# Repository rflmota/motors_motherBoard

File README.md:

# motors_motherBoard
## Carrier board for dual *[STM's L6470](https://www.st.com/en/motor-drivers/l6470.html)* stepper motor driver controller with *[Teensy 3.6](https://www.pjrc.com/teensy/)* interface. This project was applied for control a two-wheel differential drive mobile robot.

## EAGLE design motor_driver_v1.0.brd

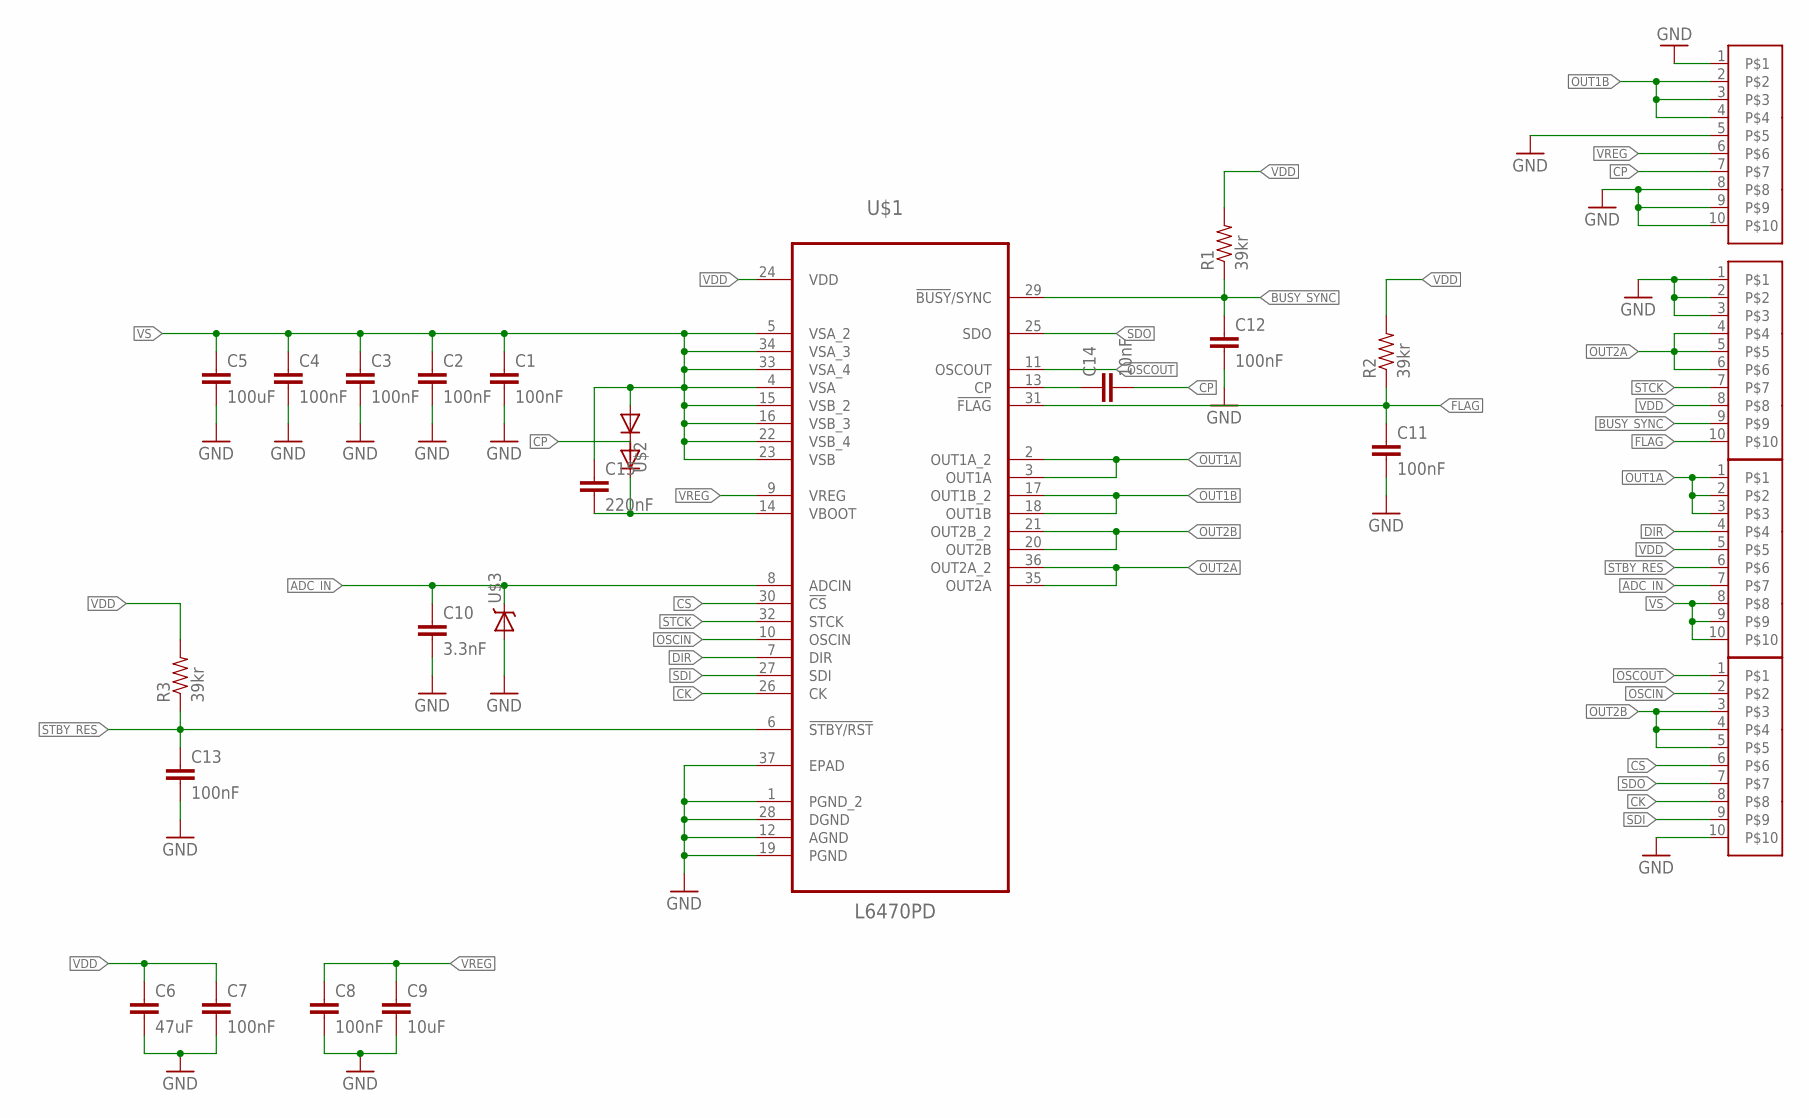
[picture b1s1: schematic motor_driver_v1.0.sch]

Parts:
C1, C2, C3, C4, C7, C8, C11, C12, C13: 100nF; 0603-CAP
C5: 100uF; CAP-10X12
C6: 47uF; 1206-CAP
C9: 10uF; 0805-CAP
C10: 3.3nF; 0603-CAP
C14: 10nF; 0603-CAP
C15: 220nF; 0603-CAP
R1, R2, R3: 39kr; 0603-RES
U$1: L6470PD; SOP65P1400X360-37N
U$2: BAV99
U$3: BZX585
U$4, U$5, U$6, U$7: CON_TH_10PINS; CON_TH_10POS

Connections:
ADC_IN: C10.P$1 (1), U$1.8 (ADCIN), U$3.P$1 (1), U$4.7
BUSY_SYNC: C12.P$1 (1), R1.1, U$1.29 (!BUSY!/SYNC), U$5.9
CK: U$1.26 (CK), U$7.8
CP: C14.P$2 (2), U$2.P$3 (3), U$6.7
CS: U$1.30 (!CS), U$7.6
DIR: U$1.7 (DIR), U$4.4
FLAG: C11.P$1 (1), R2.1, U$1.31 (!FLAG), U$5.10
GND: C1.P$2 (2), C2.P$2 (2), C3.P$2 (2), C4.P$2 (2), C5.P$2 (2), C6.P$2 (2), C7.P$2 (2), C8.P$2 (2), C9.P$2 (2), C10.P$2 (2), C11.P$2 (2), C12.P$2 (2), C13.P$2 (2), U$1.1 (PGND_2), U$1.12 (AGND), U$1.19 (PGND), U$1.28 (DGND), U$1.37 (EPAD), U$3.P$2 (2), U$5.1, U$5.2, U$5.3, U$6.1, U$6.5, U$6.8, U$6.9, U$6.10, U$7.10
unnamed: C15.P$2 (2), U$1.14 (VBOOT), U$2.P$2 (2)
unnamed: C14.P$1 (1), U$1.13 (CP)
OSCIN: U$1.10 (OSCIN), U$7.2
OSCOUT: U$1.11 (OSCOUT), U$7.1
OUT1A: U$1.2 (OUT1A_2), U$1.3 (OUT1A), U$4.1, U$4.2, U$4.3
OUT1B: U$1.17 (OUT1B_2), U$1.18 (OUT1B), U$6.2, U$6.3, U$6.4
OUT2A: U$1.35 (OUT2A), U$1.36 (OUT2A_2), U$5.4, U$5.5, U$5.6
OUT2B: U$1.20 (OUT2B), U$1.21 (OUT2B_2), U$7.3, U$7.4, U$7.5
SDI: U$1.27 (SDI), U$7.9
SDO: U$1.25 (SDO), U$7.7
STBY_RES: C13.P$1 (1), R3.1, U$1.6 (!STBY/RST), U$4.6
STCK: U$1.32 (STCK), U$5.7
VDD: C6.P$1 (1), C7.P$1 (1), R1.2, R2.2, R3.2, U$1.24 (VDD), U$4.5, U$5.8
VREG: C8.P$1 (1), C9.P$1 (1), U$1.9 (VREG), U$6.6
VS: C1.P$1 (1), C2.P$1 (1), C3.P$1 (1), C4.P$1 (1), C5.P$1 (1), C15.P$1 (1), U$1.4 (VSA), U$1.5 (VSA_2), U$1.15 (VSB_2), U$1.16 (VSB_3), U$1.22 (VSB_4), U$1.23 (VSB), U$1.33 (VSA_4), U$1.34 (VSA_3), U$2.P$1 (1), U$4.8, U$4.9, U$4.10

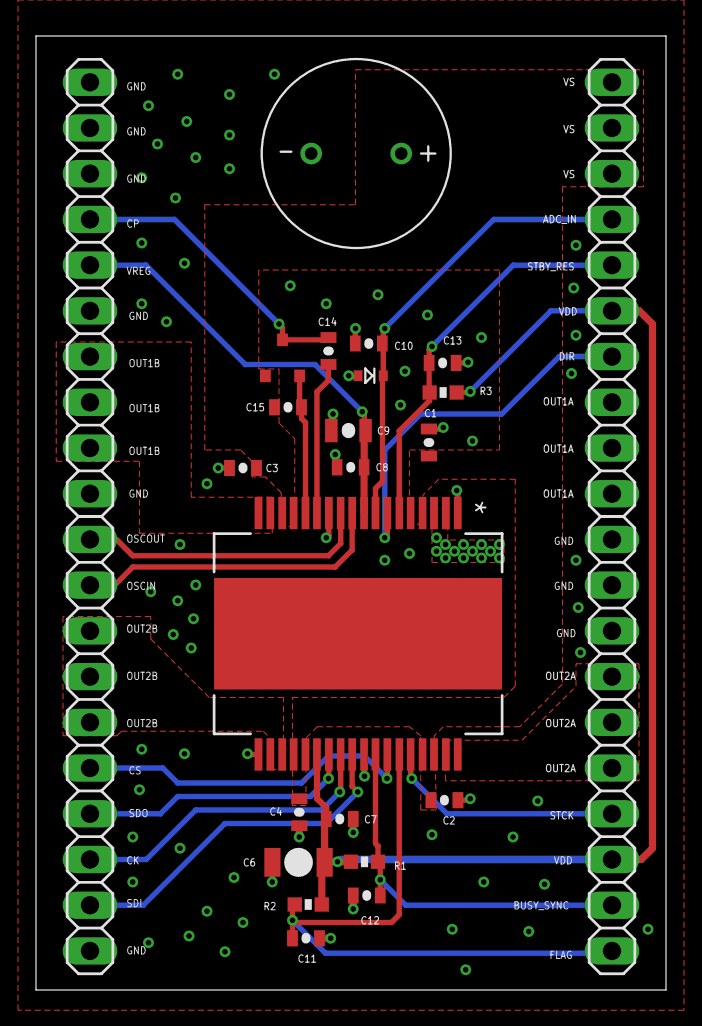
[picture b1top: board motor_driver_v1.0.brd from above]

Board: 2 copper layers, 35.0 x 53.0 mm, 25 parts (0 on the bottom side), 23 nets.

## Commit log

2019-05-23 Edited README
